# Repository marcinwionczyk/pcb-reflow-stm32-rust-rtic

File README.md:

# pcb-reflow-stm32-rust-rtic
This is how the reflow process look like:
https://youtu.be/pWV79pceqmc?si=kS1UuS4xw2wpDsws

## Software

Rust code for STM32F411RCT6 microcontroller to drive PCB reflow solder plate.
Code is based on https://github.com/gabrielvegamotta/PCB-Reflow/blob/main/V1-Arduino-PTH/Firmware/PCB_Reflow_V1.6.ino

Base of the code was generated with command: 
`cargo generate --git https://github.com/burrbull/stm32-template/`

In order to build it, you need to prepare your environment according to:
https://docs.rust-embedded.org/book/intro/install.html

and issue a command within this folder:
- `cargo build --release` for release version
- `cargo build` for unoptimised, debug version

Then you may run software on microcontroller with `cargo run` and flash it via STLink device with 
`cargo flash --release --chip STM32F411RCT6x`  
## Hardware
This is how the PCB top layer look like:

Here you have [schematics in PDF](./docs/hardware/mainboard_v3.pdf)

Some major parts:
1. MAX6675 as a temperature sensor. You can get it for example from here:
https://botland.store/high-precision-temperature-sensors/12504-max6675-thermocouple-spi-temperature-sensor-5904422307868.html
2. TC2004A LCD Character screen: https://botland.store/alphanumeric-and-graphic-displays/19736-lcd-display-4x20-characters-green-with-connectors-justpi-5903351243087.html
3. PCF8574 as I2C port expander
4. SWT-11136 buttons: https://botland.store/tact-switch/11138-tact-switch-12x12mm-cap-black-5-pieces-5904422307530.html
5. 
6. micromatch connectors (I have plenty of them)

PCB was designed with Autodesk EAGLE. 
- [schematics](./docs/hardware/mainboard_v3.sch)
- [PCB project](./docs/hardware/mainboard_v3.brd)

I power it with +12V DC.
If you want to order a PCB, here you have [gerber files](./docs/hardware/mainboard_v3_2023-11-27.zip)

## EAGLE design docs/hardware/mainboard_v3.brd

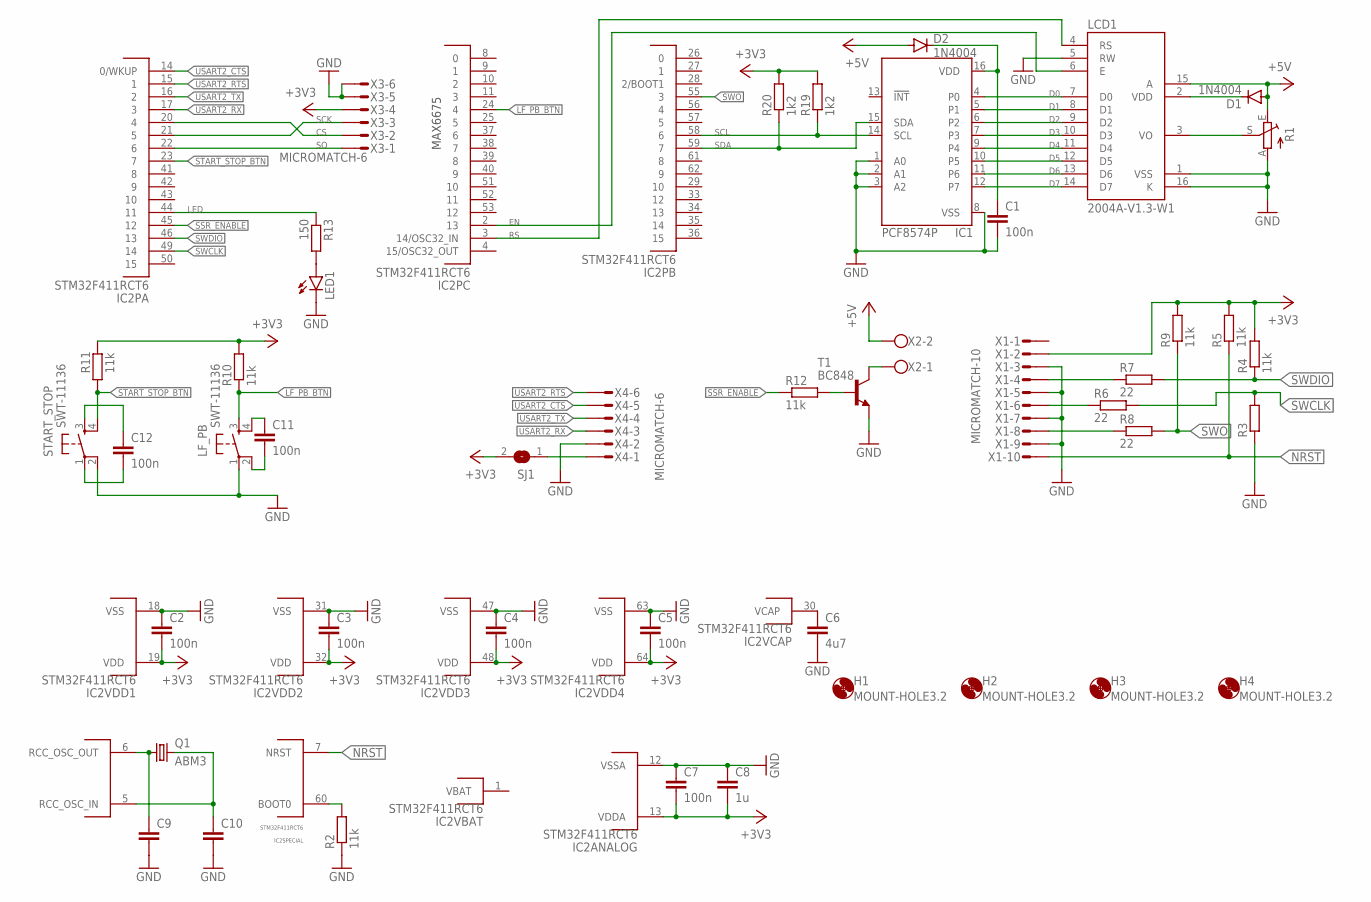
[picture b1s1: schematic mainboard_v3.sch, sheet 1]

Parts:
C1, C2, C3, C4, C5, C7, C11, C12: 100n; C0805
C6: 4u7; C0805
C8: 1u; C0805
C9, C10: C-EUC0805; C0805
D1, D2: 1N4004; DO41-10
H1, H2, H3, H4: MOUNT-HOLE3.2; 3,2
IC1: PCF8574P; DIL16
IC2: STM32F411RCT6; QFP50P1200X1200X160-64N
LCD1: 2004A-V1.3-W1
LED1: LED5MM
LF_PB: SWT-11136
Q1: ABM3; XTALDFN500X320X130-2N
R1: TRIM_EU-CA9V; CA9V
R2, R4, R5, R9, R10, R11, R12: 11k; R1206
R3: R-EU_R1206; R1206
R6, R7, R8: 22; R0603
R13: 150; R0805
R19, R20: 1k2; 0207/12
SJ1: SJ
START_STOP: SWT-11136
T1: BC848; SOT23
X1: MICROMATCH-10
X2: W237-102
X3, X4: MICROMATCH-6

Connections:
2: IC2.54 (2)
+3V3: C2.2, C3.2, C4.2, C5.2, C7.2, C8.2, IC2.13 (VDDA), IC2.19 (VDD), IC2.32 (VDD), IC2.48 (VDD), IC2.64 (VDD), R4.2, R5.2, R9.2, R10.2, R11.2, R19.2, R20.2, SJ1.2, X1.2, X3.4; also elsewhere on the board
+5V: D1.A, D2.A, LCD1.15 (A), R1.E, X2.2; also elsewhere on the board
CS: IC2.20 (4), X3.2
D0: IC1.4 (P0), LCD1.7 (D0)
D1: IC1.5 (P1), LCD1.8 (D1)
D2: IC1.6 (P2), LCD1.9 (D2)
D3: IC1.7 (P3), LCD1.10 (D3)
D4: IC1.9 (P4), LCD1.11 (D4)
D5: IC1.10 (P5), LCD1.12 (D5)
D6: IC1.11 (P6), LCD1.13 (D6)
D7: IC1.12 (P7), LCD1.14 (D7)
EN: IC2.2 (13), LCD1.6 (E)
GND: C1.2, C2.1, C3.1, C4.1, C5.1, C6.2, C7.1, C8.1, C9.2, C10.2, IC1.1 (A0), IC1.2 (A1), IC1.3 (A2), IC1.8 (VSS), IC2.12 (VSSA), IC2.18 (VSS), IC2.31 (VSS), IC2.47 (VSS), IC2.63 (VSS), LCD1.1 (VSS), LCD1.5 (RW), LCD1.16 (K), LED1.K (C), LF_PB.1, R1.A, R2.1, R3.1, START_STOP.2 (P1), T1.2 (E), X1.3, X1.5, X1.7, X1.9, X3.5, X3.6, X4.2; also elsewhere on the board
LED: IC2.44 (11), R13.1
LF_PB_BTN: IC2.24 (4), LF_PB.3 (S), R10.1
unnamed: IC2.60 (BOOT0), R2.2
unnamed: C1.1, D2.C, IC1.16 (VDD)
unnamed: C10.1, IC2.5 (RCC_OSC_IN), Q1.2
unnamed: C9.1, IC2.6 (RCC_OSC_OUT), Q1.1
unnamed: R7.1, X1.4
unnamed: R6.1, X1.6
unnamed: R8.1, X1.8
unnamed: LCD1.3 (VO), R1.S
unnamed: C6.1, IC2.30 (VCAP)
unnamed: T1.3 (C), X2.1
unnamed: R12.2, T1.1 (B)
unnamed: LED1.A, R13.2
unnamed: C12.2, START_STOP.1
unnamed: C11.2, LF_PB.2 (P1)
unnamed: C11.1, LF_PB.4 (S1)
unnamed: C12.1, START_STOP.3 (S)
unnamed: D1.C, LCD1.2 (VDD)
unnamed: SJ1.1, X4.1
NRST: IC2.7 (NRST), R5.1, X1.10
RS: IC2.3 (14/OSC32_IN), LCD1.4 (RS)
SCK: IC2.21 (5), X3.3
SCL: IC1.14 (SCL), IC2.58 (6), R19.1
SDA: IC1.15 (SDA), IC2.59 (7), R20.1
SO: IC2.22 (6), X3.1
SSR_ENABLE: IC2.45 (12), R12.1
START_STOP_BTN: IC2.23 (7), R11.1, START_STOP.4 (S1)
SWCLK: IC2.49 (14), R3.2, R6.2
SWDIO: IC2.46 (13), R4.1, R7.2
SWO: IC2.55 (3), R8.2, R9.1
USART2_CTS: IC2.14 (0/WKUP), X4.5
USART2_RTS: IC2.15 (1), X4.6
USART2_RX: IC2.17 (3), X4.3
USART2_TX: IC2.16 (2), X4.4
VBAT: IC2.1 (VBAT)

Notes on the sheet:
MAX6675

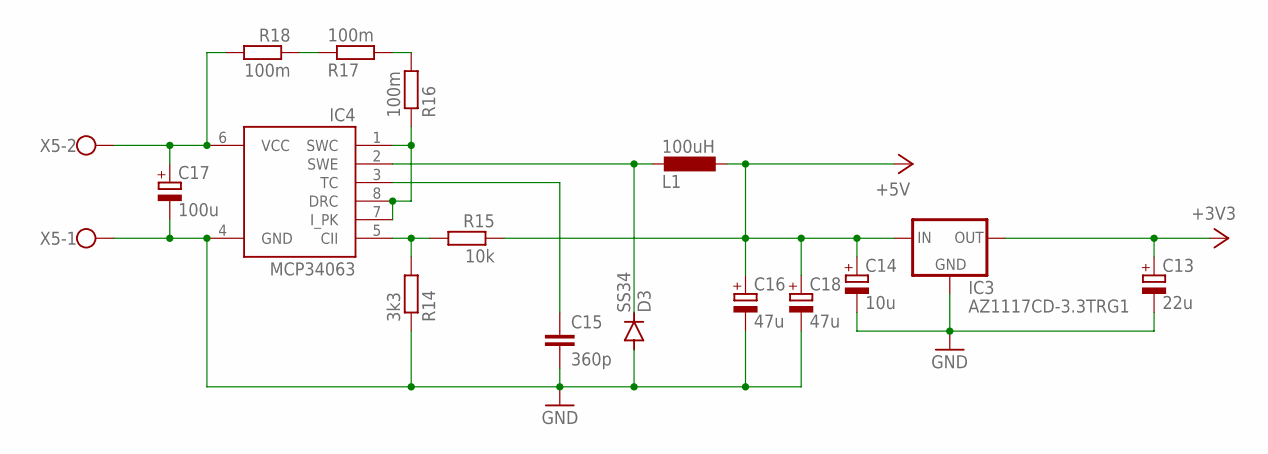
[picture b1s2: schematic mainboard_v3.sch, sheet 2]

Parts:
C13: 22u; SMC_B
C14: 10u; SMC_A
C15: 360p; C1206
C16, C18: 47u; SMC_D
C17: 100u; E5-8,5
D3: SS34; SMB
IC3: AZ1117CD-3.3TRG1; TO228P1014X240-3N
IC4: MCP34063; SOIC127P600X175-8N
L1: 100uH; INDM7770X500N
R14: 3k3; R1206
R15: 10k; R1206
R16, R17, R18: 100m; 0309/12
X5: W237-102

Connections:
+3V3: C13.+, IC3.3 (OUT); also elsewhere on the board
+5V: C14.+, C16.+, C18.+, IC3.2 (IN), L1.1, R15.1; also elsewhere on the board
GND: C13.-, C14.-, C15.2, C16.-, C17.-, C18.-, D3.A, IC3.1 (GND), IC4.4 (GND), R14.1, X5.1; also elsewhere on the board
unnamed: IC4.1 (SWC), IC4.7 (I_PK), IC4.8 (DRC), R16.1
unnamed: C15.1, IC4.3 (TC)
unnamed: D3.C, IC4.2 (SWE), L1.2
unnamed: IC4.5 (CII), R14.2, R15.2
unnamed: R16.2, R17.2
unnamed: R17.1, R18.1
unnamed: C17.+, IC4.6 (VCC), R18.2, X5.2

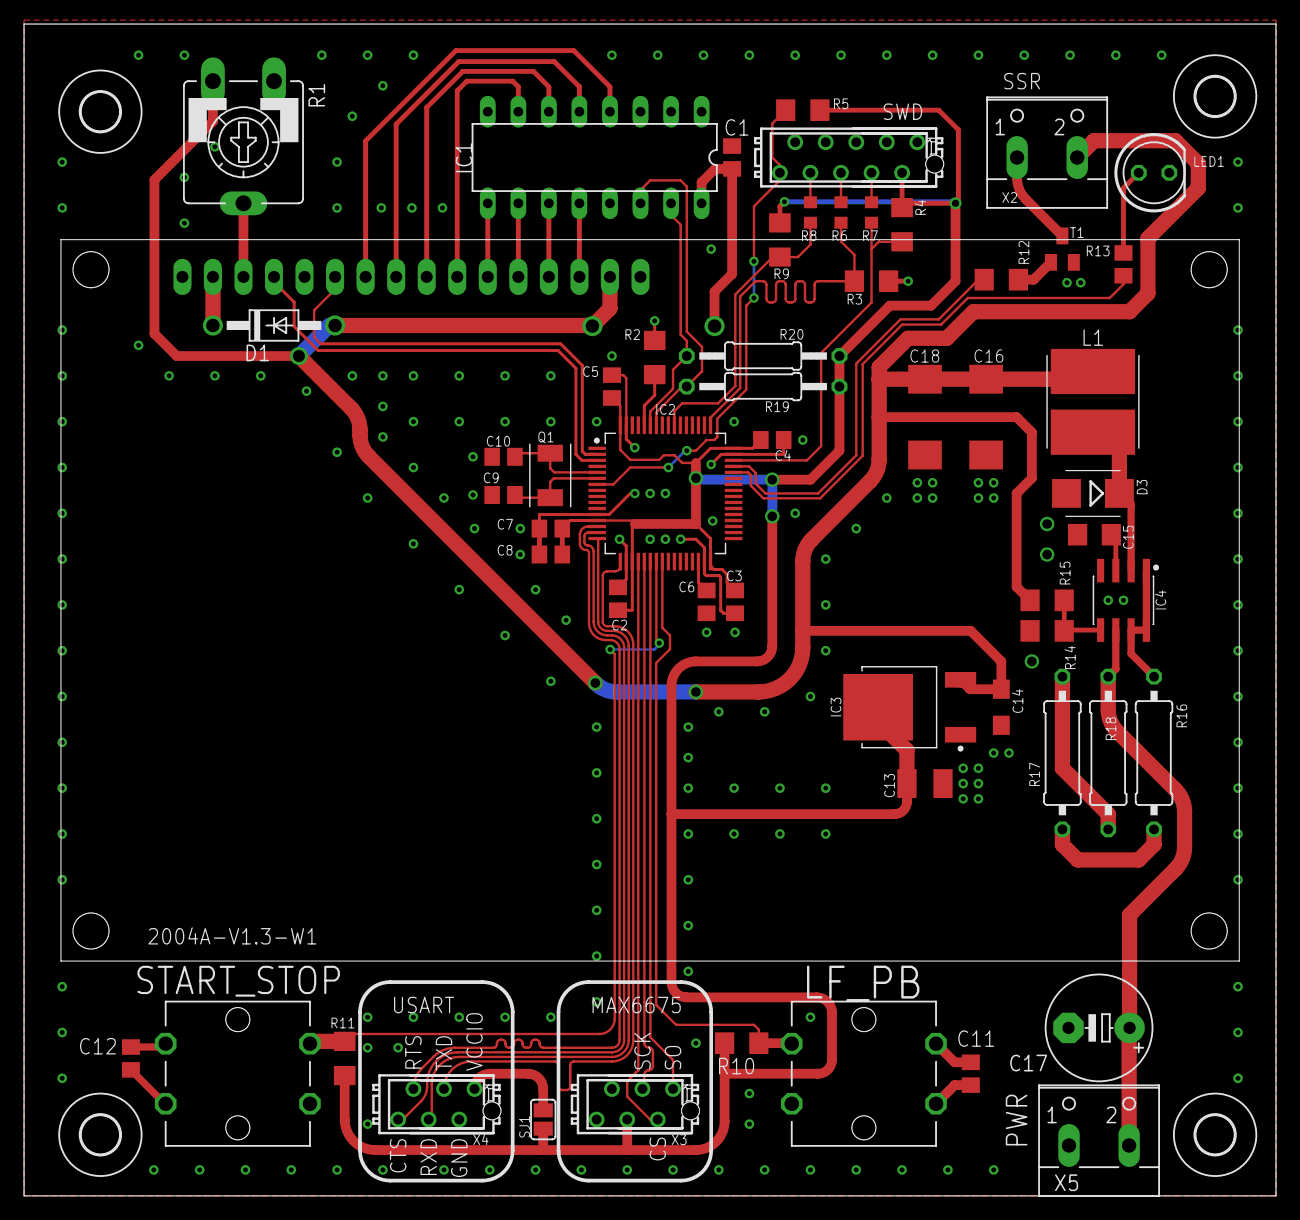
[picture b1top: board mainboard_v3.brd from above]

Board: 2 copper layers, 104.1 x 97.5 mm, 62 parts (1 on the bottom side), 55 nets.

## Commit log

2023-11-10 added some images
2023-11-10 fixed readme
2023-11-17 added display code
2023-11-17 added reading temperature from MAX6675
2023-11-17 removed display_old.rs
2023-11-19 init task done
2023-11-21 figured out how to continue without delays
2023-11-21 almost done. I need to make logging go to serial and test this.
2023-11-26 Display works. Buttons does not work.
2023-11-26 added setup image
2023-11-26 buttons work
2023-11-27 everything works
2023-11-27 final commit
2023-11-27 modified README
2023-11-27 fixed PID controller
2023-11-28 added comment
2023-11-28 The PTC heater was heating to fast and I had to low temperature readings from thermocouple an MAX6675. Kind of solved it by togling ssr_pin instead of setting it high.
2023-11-28 changed Readme
2023-12-01 - slowed down temperature rise of a heating element with ssr_counter variable - adjusted shown temperature with some correcting function (main.rs, line 264)
2023-12-03 changed linker in config.toml
